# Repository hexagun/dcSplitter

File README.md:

# dcSplitter
This is a simple DC splitter providing 12V, 5V, 3.3V supply for breadboard. The project is built using KiCad.

## About dcSplitter:
This dcSplitter gives different outputs based on 12 V input supply through a DC jack. On one end there is 12V and 3.3V and on other end there is 12V and 5V supply lines.
The combinations that can be used are as:
1. 12V - 5V
2. 3.3V - 12V
3. 3.3V - 5V
4. 12V - 12V

## How To Use:
There are jumpers which you can use to connect a particular supply. Two jumpers should be used for higher current applications.

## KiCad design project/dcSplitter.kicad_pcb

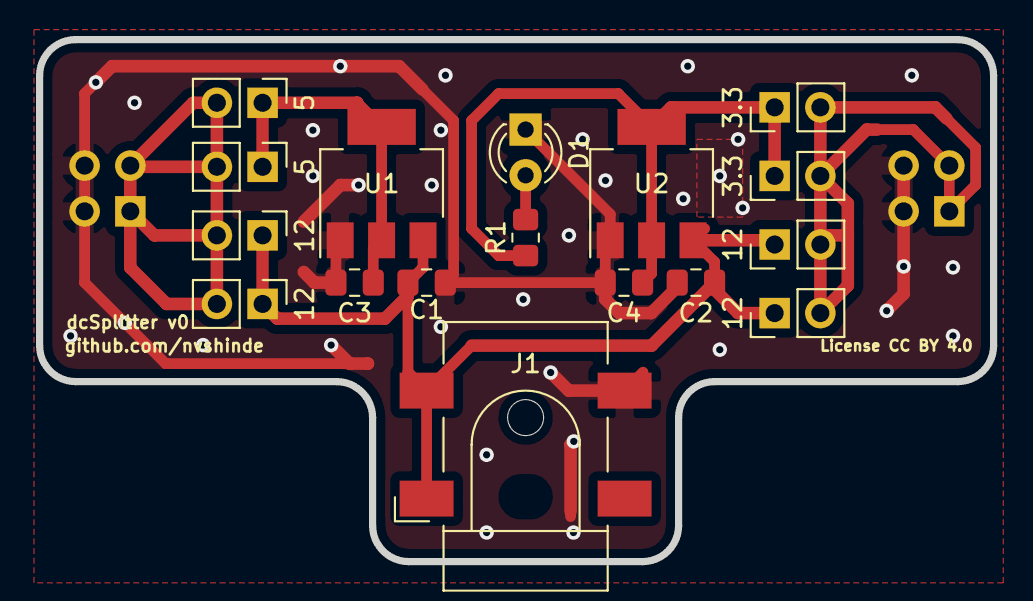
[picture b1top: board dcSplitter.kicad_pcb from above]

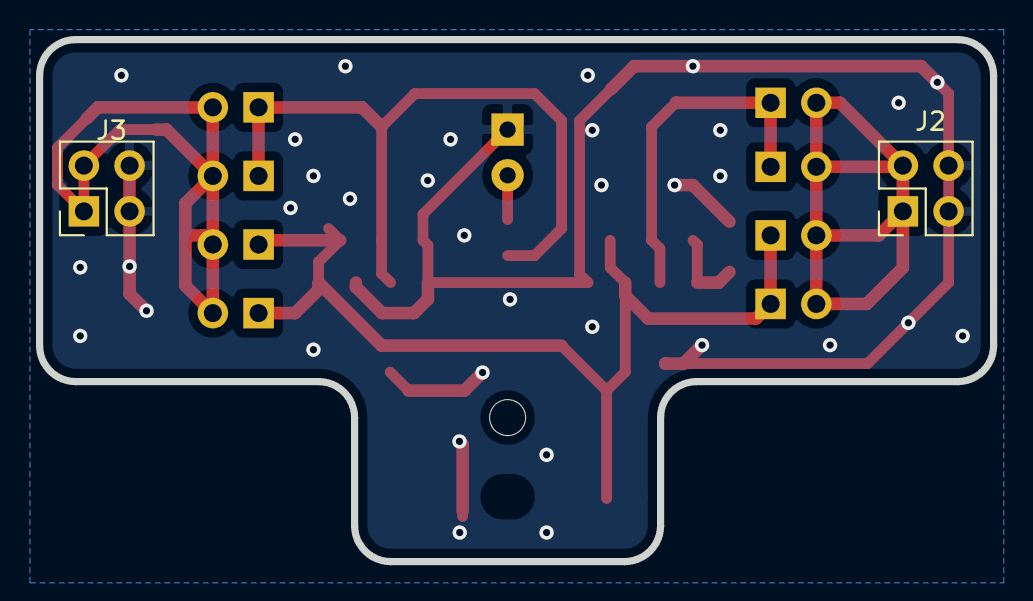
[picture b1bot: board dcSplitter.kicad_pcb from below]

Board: 2 copper layers, 53.0 x 29.0 mm, 19 parts (2 on the bottom side), 7 nets.

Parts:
3.3, 3.3#2: 3.3; PinHeader_1x02_P2.54mm_Vertical
5, 5#2: 5; PinHeader_1x02_P2.54mm_Vertical
12, 12#2, 12#3, 12#4: 12; PinHeader_1x02_P2.54mm_Vertical
C1, C2: 10uF; C_0805_2012Metric_Pad1.18x1.45mm_HandSolder
C3, C4: 22uF; C_0805_2012Metric_Pad1.18x1.45mm_HandSolder
D1: LED; LED_D3.0mm
J1: Barrel_Jack; BarrelJack_CLIFF_FC681465S_SMT_Horizontal
J2, J3: Conn_02x02_Odd_Even; PinHeader_2x02_P2.54mm_Vertical
R1: 1k; R_0805_2012Metric_Pad1.20x1.40mm_HandSolder
U1: AZ1117-5.0; SOT-223-3_TabPin2
U2: AZ1117-3.3; SOT-223-3_TabPin2

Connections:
GND: C1.2, C2.2, C3.2, C4.2, D1.1, J1.2, J2.3, J2.4, J3.3, J3.4, U1.1, U2.1
unnamed: 12.1, 12#2.1, 12#3.1, 12#4.1, C1.1, C2.1, J1.1, U1.3, U2.3
unnamed: 5.1, 5#2.1, C3.1, U1.2
unnamed: 3.3.1, 3.3#2.1, C4.1, R1.1, U2.2
unnamed: D1.2, R1.2
unnamed: 5.2, 5#2.2, 12#3.2, 12#4.2, J2.1, J2.2
unnamed: 3.3.2, 3.3#2.2, 12.2, 12#2.2, J3.1, J3.2

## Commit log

2021-04-18 Added schematic file
2021-04-18 Added Layout file
2021-04-18 Layout add
2021-04-18 project files

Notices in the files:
project/dcSplitter.kicad_pcb:
License CC BY 4.0
